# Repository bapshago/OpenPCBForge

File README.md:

# pcbforge

A code-first PCB pipeline with Claude on top. You describe a circuit in
Python (or in plain English, and Claude writes the Python), and pcbforge turns
it into a routed, DRC-checked board plus fab-ready Gerbers.

```
design.py (SKiDL)  ──▶ netlist ──▶ .kicad_pcb (pcbnew API: footprints, outline, placement)
                   ──▶ Freerouting (autoroute via Specctra DSN/SES)
                   ──▶ kicad-cli DRC (JSON) ──▶ Claude reads it and fixes the design
                   ──▶ kicad-cli Gerbers + drill + pick-and-place ──▶ zip
                   ──▶ gerbonara SVG preview of the Gerbers
```

KiCad does the hard geometry: footprints, routing and rule checks. Claude does
what it's good at: turning a spec into a correct circuit, choosing parts,
reading DRC reports and iterating.

**New here?** [`docs/user_guide.md`](docs/user_guide.md) explains, step by step, how to get a
board designed, ordered, built and tested by working with Claude. No setup needed for that.

## Setup

**Ubuntu 24.04:** `./scripts/setup_ubuntu.sh` installs KiCad 9, its libraries,
Java 25 and Freerouting, and creates `.venv`.

**macOS / Windows:** install KiCad 9 from kicad.org and Java 25+ (for
example Temurin), then:

```bash
./scripts/get_freerouting.sh
# Use KiCad's bundled Python so `import pcbnew` works:
#   macOS:   /Applications/KiCad/KiCad.app/Contents/Frameworks/Python.framework/Versions/Current/bin/python3
#   Windows: "C:\Program Files\KiCad\9.0\bin\python.exe"
<kicad-python> -m venv --system-site-packages .venv
.venv/bin/pip install -e '.[dev]'
```

Check that it works: `pytest` runs the blinky board through the full pipeline.

## Usage

```bash
# Build a design file by hand
pcbforge build designs/blinky.py
#   blinky: 3 parts, 3 nets, routed=True
#   DRC: 0 errors, 0 warnings, 0 unconnected
#   Gerbers: build/blinky/blinky-gerbers.zip

# Let Claude design one (needs ANTHROPIC_API_KEY or `ant auth login`)
pcbforge agent "A 30x20mm board: 2-pin header for 5V in, a power LED with a resistor, \
and a tactile button that pulls a 3-pin header's signal pin to ground"
```

Open `build/<name>/<name>.kicad_pcb` in KiCad to inspect or hand-tune the
board. Upload `build/<name>/<name>-gerbers.zip` to your fab (JLCPCB, PCBWay,
OSH Park, and so on). For JLCPCB assembly, also upload `<name>-bom-jlc.csv`
and `<name>-cpl-jlc.csv`.

The agent shows each generated design file and asks before running it,
because a design file is Python that gets executed. `--auto-approve` skips
the prompt.

## JLCPCB files for an existing board

`pcbforge jlc` makes a JLCPCB BOM and CPL (and fresh Gerbers) straight from any
`.kicad_pcb`, including boards drawn by hand or imported from Altium, PADS or Eagle:

```bash
pcbforge jlc path/to/board.kicad_pcb --out build \
    --value-field ALTIUM_VALUE   # field holding the real value, if Value is a placeholder
    --include Q4                 # place a part that also has through-hole pads (e.g. TO-220/DPAK)
    --exclude R99                # leave a part out
    --rotate U7=270              # per-part JLCPCB rotation fix (repeatable)
    --rotate-fp 0805=270         # rotation fix for every part with that footprint name (repeatable)
    --offset=-48.5,200.0         # shift the CPL to match Gerbers made in another tool
    --lcsc L1=C130293            # LCSC number for parts matched by hand (repeatable; R1,R2=C17414 works)
    --move Q4=0,-4.4             # shift one part in the CPL (mm, +y up), e.g. a TO-220/DPAK combo footprint
    --set-value Q2,Q3=IRL540NS   # replace a value (a substitute part, or one the board leaves blank)
    --no-gerbers
```

Resistor and capacitor values are written the way JLCPCB's BOM check reads them
(`4k7` -> `4.7kΩ`, `240R` -> `240Ω`, `100n` -> `100nF`, `2u2` -> `2.2uF`); `--raw-values`
keeps them as drawn. Design-file BOMs from `pcbforge build` get the same treatment.

It places every part whose pads are all SMD, at the centre of its SMD pads (imported
footprints don't always put the origin there), skips values that mean "not fitted"
(na, DNP, ...), and prints what it left out and why: through-hole parts, mixed
SMD/through-hole footprints, and parts with a missing or unknown value.

## JLCPCB parts check

With your own **JLCPCB API key for the parts endpoints** (created at api.jlcpcb.com:
Console → Manage Apps → an app with the Parts APIs approved → Access Key → Create), pcbforge
checks every LCSC number against JLCPCB's records: package against footprint, value, stock
and basic/extended type. Put `JLC_APP_ID`, `JLC_ACCESS_KEY` and `JLC_SECRET_KEY` in `.env`, then:

```bash
pcbforge jlc-auth                                   # check the keys (never prints them)
pcbforge parts-check fab/<board>_rev_a/<board>-bom-jlc.csv [--boards N]
pcbforge jlc-part C25741                            # JLCPCB's full record for a part
```

`pcbforge build` runs the same check when the keys are set. Details and troubleshooting:
`docs/jlcpcb_api.md`.

## Writing a design file

See `designs/blinky.py` for the minimum and `designs/signal_module_928.py`
for a full board. A design file defines:

| Name | Required | Meaning |
|---|---|---|
| `build()` | yes | Creates SKiDL `Part`s (each with `ref=` and `footprint="Lib:Name"`) and connects `Net`s |
| `BOARD` | no | Board settings, below; the origin is top-left with y pointing down |
| `PLACEMENT` | no | `{ref: (x_mm, y_mm, rotation_deg)}`; parts without an entry go on a grid |

`BOARD` keys:

| Key | Meaning |
|---|---|
| `width_mm`, `height_mm` | Board size (a rectangle unless `outline` is given) |
| `outline` | `[(x, y), ...]` closed polygon for a custom shape |
| `holes` | `[(x, y), ...]` M3 mounting holes (`hole_footprint` to change) |
| `silk` | `[(x, y, text, size_mm, rotation), ...]` silkscreen labels |
| `hide_silk_refs` | `True` hides reference designators on the silkscreen (dense boards) |
| `route_passes` | Freerouting passes (default 20; busy boards need more) |
| `clearance_mm` | Copper clearance for every net, default 0.2 mm. 0.15 suits 0.5 mm-pitch ICs (JLCPCB's 2-layer minimum is about 0.127 mm) |
| `route_attempts` | Fresh routing tries, keeping the most complete (default 1) |
| `ground_pour` | Net name, e.g. `"GND"`, to pour on both layers after routing |
| `pour_keepouts` | `[(x1, y1, x2, y2), ...]` areas kept free of poured copper (antennas) |
| `jlc_rotations` | `[(footprint_regex, degrees), ...]` extra JLCPCB placement-rotation fixes, checked before the built-in table in `pcbforge/jlc.py` |
| `jlc_ref_rotations` | `{ref: degrees}` per-part JLCPCB rotation fixes, for parts whose model differs from others in the same package |

Footprints are KiCad 9 library names (`Lib:Name`). `footprints/pcbforge.pretty` holds KiCad
footprints adapted for JLCPCB (for example thermal vias opened to 0.3 mm); use them as
`pcbforge:Name`. See `footprints/README.md`.

Put `part.fields["LCSC"] = "C12084"` (and optionally `"MPN"`) on a part to
carry its LCSC number into the JLCPCB BOM.

**Parts catalogue** (`pcbforge/parts.py`): every part already ordered or checked at JLCPCB,
with its LCSC number. A design can pick one by name (`part(..., **parts.pick("res_0603_10k"))`),
and any part without an LCSC number of its own gets the catalogue's part for its footprint and
value automatically. Each build also writes `<name>-jlc-parts.md`: every BOM line with its LCSC
link, and for parts still to choose, search terms plus JLCPCB and LCSC search links. The BOM's
Footprint column uses JLCPCB's package names (`0603`, `SOIC-8`, `XH-3A 2.5mm`), not KiCad's.

Working on this repo as Claude? Read `docs/claude_playbook.md` first: how boards get
designed, ordered, brought up and documented here, with lessons from the first boards.

## Boards in this repo

| Board | Design | Fab snapshot | Notes |
|---|---|---|---|
| 928 Signal Module rev A (**installed in the '81**, Nov 1 2026) | `designs/signal_module_928.py` | `fab/signal_module_928_rev_a/` | `docs/signal_module_928_handoff.md`, firmware in `firmware/signal_module_928/` |
| 928 Heater Controller rev A (in production) | `designs/heater_controller_928.py` | `fab/heater_controller_928_rev_a/` | `docs/heater_controller_928.md` |
| `designs/blinky.py` | the smallest example: 3 parts | built by `pytest` | |

The two 928 boards were made for a 1981 Porsche 928 converted to a Nissan Leaf drivetrain, and
share a 60 x 90 mm outline and mounting holes. They're real, ordered boards, included as
worked examples: a design file, the exact files sent to JLCPCB, and a connection test
(`tests/test_<board>.py`) that checks every pin against the datasheets. The signal module's
hardware and firmware are also published on their own at
[bapshago/928-Signal-Board](https://github.com/bapshago/928-Signal-Board).

## Layout

| Path | Role |
|---|---|
| `pcbforge/netlist.py` | Runs the design file with SKiDL, then ERC and netlist |
| `pcbforge/board.py` | Builds the `.kicad_pcb` with pcbnew: outline, nets, footprints, placement |
| `pcbforge/route.py` | Freerouting round-trip |
| `pcbforge/pour.py` | Optional ground pour with keepouts |
| `pcbforge/drc.py` | `kicad-cli pcb drc`, summarized |
| `pcbforge/export.py` | Gerbers, drill file, pick-and-place, zip |
| `pcbforge/jlc.py` | JLCPCB BOM, CPL and parts list |
| `pcbforge/parts.py` | Parts catalogue: parts already ordered at JLCPCB, used by default |
| `pcbforge/jlcapi.py`, `pcbforge/partcheck.py` | JLCPCB Open API client and part check: package, value and stock of every LCSC number (`pcbforge parts-check`; see `docs/jlcpcb_api.md`) |
| `pcbforge/preview.py` | Renders the Gerbers to SVG with gerbonara |
| `pcbforge/pipeline.py` | Runs all of the above in order |
| `pcbforge/agent.py` | Claude tool-use agent (symbol/footprint lookup, write design, build) |
| `pcbforge/env.py` | KiCad paths and tool locations, each overridable by env var |

## Good next steps

1. **Smarter placement.** Group parts by net connectivity (force-directed
   placement or simulated annealing) so routes are short. Have Claude supply
   the constraints ("decoupling caps next to U1's VDD pins", "connectors on
   the edge") rather than coordinates.
2. **Schematic output.** SKiDL can generate KiCad schematics, which makes
   human review much easier.
3. **Net classes.** Wider traces for power nets (design settings) before routing.
4. **Part search for the agent.** The JLCPCB parts check is done (`docs/jlcpcb_api.md`);
   next, a local copy of JLCPCB's catalogue so the agent can search it for parts.
5. **Fab-specific DRC.** Load your fab's design rules (`.kicad_dru`) so DRC
   matches what they can manufacture.

## Gotchas

- **Java version:** Freerouting 2.4 needs Java 25+. Set `JAVA=/path/to/java25`
  if the default `java` is older.
- **SKiDL tool version:** SKiDL defaults to KiCad 10 libraries. pcbforge pins
  KiCad 9; change `SKIDL_TOOL` when you upgrade.
- **`pcbnew` import errors:** the venv must use the same Python that KiCad was
  built against, with `--system-site-packages`.

## Built on

pcbforge is mostly glue between these projects, and wouldn't exist without them. Thank you
to their authors and maintainers.

| Project | What it does in pcbforge | License |
|---|---|---|
| [SKiDL](https://github.com/devbisme/skidl) by Dave Vandenbout | Runs the Python design file: parts, nets, the electrical rules check (ERC) and the netlist | MIT |
| [KiCad](https://www.kicad.org) | The `pcbnew` Python API builds the board; `kicad-cli` runs DRC and writes Gerbers, drill and placement files; its symbol and footprint libraries supply every part | GPL-3.0-or-later; libraries CC-BY-SA 4.0 with an exception for designs that use them |
| [Freerouting](https://github.com/freerouting/freerouting) | Autoroutes the board | GPL-3.0 |
| [gerbonara](https://gitlab.com/gerbolyze/gerbonara) by jaseg and XenGi | Renders the Gerbers to an SVG preview | Apache-2.0 |
| [Anthropic Python SDK](https://github.com/anthropics/anthropic-sdk-python) | The design agent's calls to Claude | MIT |

They're installed separately (see Setup) and keep their own licenses. The footprint in
`footprints/pcbforge.pretty` is a modified KiCad library footprint and stays under the KiCad
libraries' license.

## Contributing

pcbforge was written for one person's projects and shared in case it's useful to others.
Issues and pull requests are welcome: bug reports with the design file and the build output,
new parts for the catalogue (with their LCSC numbers and where they were checked), JLCPCB
rotation fixes confirmed in their placement preview, and the "Good next steps" above.
Run `pytest` before sending a change; it needs KiCad 9 for the board tests (they skip
without it).

## License

MIT, see [LICENSE](LICENSE). The example board designs and fab files are covered too.
The tools it builds on keep their own licenses: see Built on.

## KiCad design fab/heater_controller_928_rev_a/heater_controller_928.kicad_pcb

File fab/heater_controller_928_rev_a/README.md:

# 928 Heater Controller: board rev A fabrication snapshot

Generated by `pcbforge build designs/heater_controller_928.py`. KiCad DRC: **0 errors, 0 warnings, 0 unconnected**.

Same 60 x 90 mm outline, corner notches and M3 holes as the signal module. Built for the
ESP32-S3-DevKitC-1 (header rows 22.86 mm apart). Board notes, connector pinouts and GPIO map:
`docs/heater_controller_928.md`.

Ordered Oct 23, 2026: 5 boards (green, 1.6 mm, ENIG), all 5 assembled by JLCPCB (top side), about $127 before shipping.
The pulled files went through with no manual fixes. Every assembled part carries the LCSC number it
was ordered with. Y1 (8 MHz crystal for the MCP2515 / CAN B) was added by hand in JLCPCB's BOM tool as C57131. U7's rotation fix from JLCPCB's preview (90° clockwise) is now built into the
CPL file, so a re-order should need no manual fixes.

Nov 5, 2026: in production, after JLCPCB's hold on R21-R32 (C723496 is 01005) was fixed with C25741.
`pcbforge parts-check` on `heater_controller_928-bom-jlc.csv` passes with 0 errors.

| File | Use |
|---|---|
| `heater_controller_928.kicad_pcb` (+ `.kicad_pro`, `fp-lib-table`) | Open in KiCad 9 to inspect or hand-tune |
| `heater_controller_928-gerbers.zip` | Upload to JLCPCB as the PCB (2 layers, 1.6 mm) |
| `heater_controller_928-bom-jlc.csv` | JLCPCB assembly: BOM |
| `heater_controller_928-cpl-jlc.csv` | JLCPCB assembly: placement (CPL) |
| `heater_controller_928-bom-as-ordered.csv` | The BOM JLCPCB confirmed for the first order, for reference |
| `heater_controller_928-not-placed-by-jlc.csv` | Parts JLCPCB did not place (connectors, sockets, headers) |
| `heater_controller_928-drc.json` | KiCad rule-check report |

If you change the design file, rebuild and copy the new outputs here; this folder is a
snapshot, not regenerated automatically.

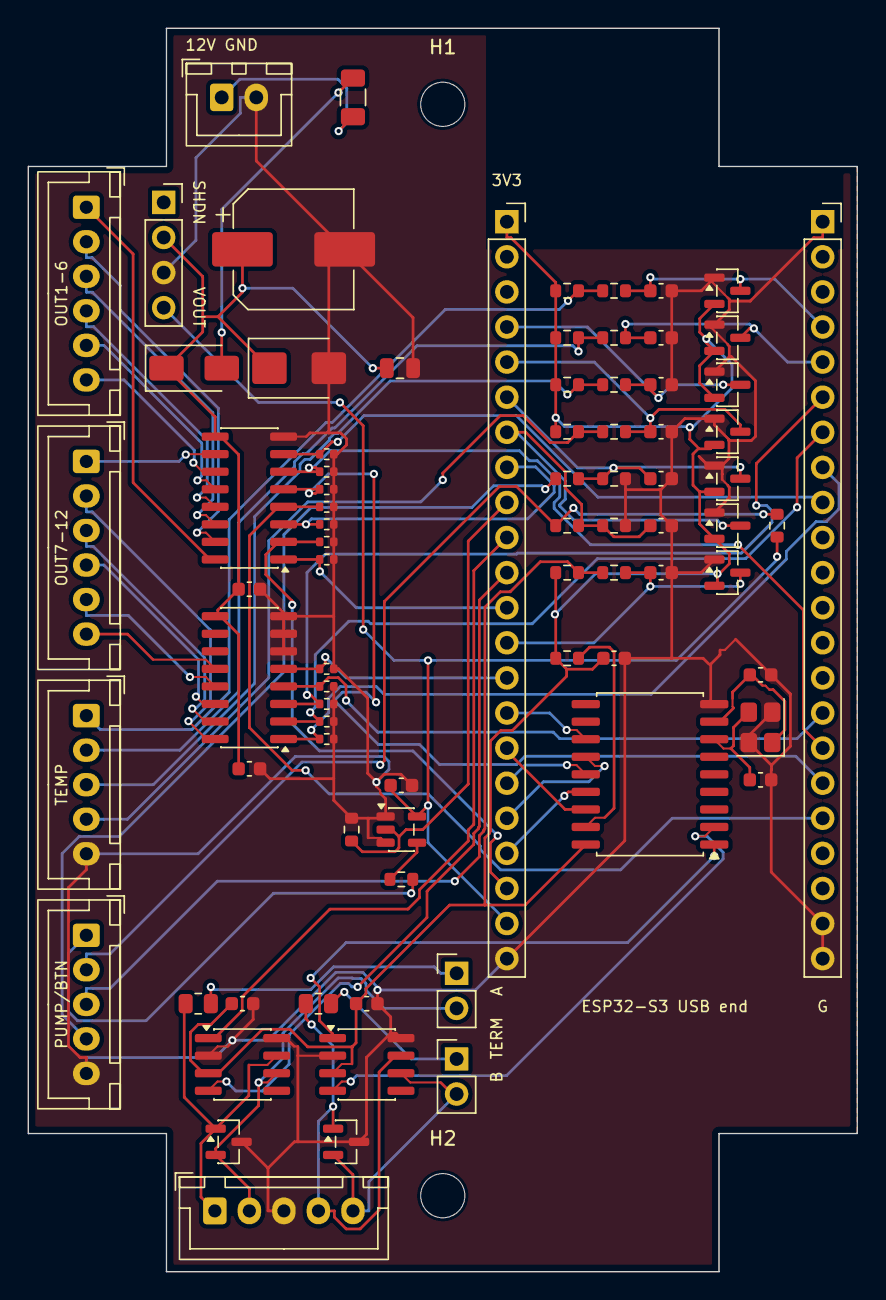
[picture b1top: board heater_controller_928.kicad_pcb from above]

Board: 2 copper layers, 60.0 x 90.0 mm, 81 parts (0 on the bottom side), 65 nets.

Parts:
C10: 47u 63V; CP_Elec_8x10.5
C11: 100n 100V; C_0805_2012Metric
C12, C13, C14, C20, C21, C41, C42, C43, C44, C51, C54: 100n; C_0603_1608Metric
C15, C16: 22p; C_0603_1608Metric
C52: 1n; C_0603_1608Metric
C53: 10n; C_0603_1608Metric
D10: SS34; D_SMA
D11: SMBJ24A; D_SMB
D20, D21: NUP2105L; SOT-23
D41, D42, D43, D44, D51, D52, D53: BAT54S; SOT-23
F1: 1A; Fuse_1206_3216Metric
H1, H2: MountingHole_3.2mm_M3
J1: PWR; JST_XH_B2B-XH-A_1x02_P2.50mm_Vertical
J2: CAN A/B; JST_XH_B5B-XH-A_1x05_P2.50mm_Vertical
J4: OUT1-6; JST_XH_B6B-XH-A_1x06_P2.50mm_Vertical
J5: OUT7-12; JST_XH_B6B-XH-A_1x06_P2.50mm_Vertical
J6: TEMP; JST_XH_B5B-XH-A_1x05_P2.50mm_Vertical
J7: PUMP/BTN; JST_XH_B5B-XH-A_1x05_P2.50mm_Vertical
J9: Pololu D36V6F5; PinSocket_1x04_P2.54mm_Vertical
J10: DevKit J1; PinSocket_1x22_P2.54mm_Vertical
J11: DevKit J3; PinSocket_1x22_P2.54mm_Vertical
JP1, JP2: TERM; PinHeader_1x02_P2.54mm_Vertical
R10, R11: 120; R_0805_2012Metric
R12, R52, R54, R56: 10k; R_0603_1608Metric
R21, R22, R23, R24, R25, R26, R27, R28, R29, R30, R31, R32: 100k; R_0402_1005Metric
R41, R43, R45, R47: 2.2k 1%; R_0603_1608Metric
R42, R44, R46, R48, R57: 1k; R_0603_1608Metric
R51: 47k; R_0603_1608Metric
R53: 4.7k; R_0603_1608Metric
R55: 22k; R_0603_1608Metric
R58: 100k; R_0603_1608Metric
R59: 100; R_0603_1608Metric
U2, U4: SN65HVD230DR; SOIC-8_3.9x4.9mm_P1.27mm
U3: MCP2515; SOIC-18W_7.5x11.6mm_P1.27mm
U5, U6: TPL7407L; SOIC-16_3.9x9.9mm_P1.27mm
U7: 74AHCT1G125; SOT-23-5
Y1: 8MHz; Crystal_SMD_3225-4Pin_3.2x2.5mm

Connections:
+3V3: C12.1, C13.1, C14.1, D41.2, D42.2, D43.2, D44.2, D51.2, D52.2, D53.2, J10.1, R12.1, R41.1, R43.1, R45.1, R47.1, R56.1, U2.3, U3.18, U4.3
+5V: C54.1, J9.4, J10.21, R53.1, U7.5
+12V_FUSED: D10.2, F1.2
+12V_IN: F1.1, J1.1
+12V_SW: C10.1, C11.1, C20.1, C21.1, D10.1, D11.1, J9.2, U5.9, U6.9
BLW_I: J4.2, U5.15
BLW_II: J4.3, U5.14
BLW_III: J4.4, U5.13
BLW_III_GPIO21: J11.18, R24.1, U5.4
BLW_II_GPIO15: J10.8, R23.1, U5.3
BLW_IV: J4.5, U5.12
BLW_IV_GPIO47: J11.17, R25.1, U5.5
BLW_I_GPIO14: J10.20, R22.1, U5.2
BLW_MASTER: J4.1, U5.16
BLW_MASTER_GPIO8: J10.12, R21.1, U5.1
BTN_GPIO3: C53.1, D53.3, J10.13, R57.2
BTN_IN: J7.3, R56.2, R57.1
CANA_H: D20.1, J2.1, R10.1, U2.7
CANA_H_TERM: JP1.1, R10.2
CANA_L: D20.2, J2.2, JP1.2, U2.6
CANA_RX_GPIO18: J10.11, U2.4
CANA_TX_GPIO17: J10.10, U2.1
CANB_H: D21.1, J2.4, R11.1, U4.7
CANB_H_TERM: JP2.1, R11.2
CANB_INT_GPIO9: J10.15, U3.12
CANB_L: D21.2, J2.5, JP2.2, U4.6
CANB_OSC1: C15.1, U3.8, Y1.1
CANB_OSC2: C16.1, U3.7, Y1.3
CANB_RESET: R12.2, U3.17
CANB_RX: U3.2, U4.4
CANB_TX: U3.1, U4.1
GND: C10.2, C11.2, C12.2, C13.2, C14.2, C15.2, C16.2, C20.2, C21.2, C41.2, C42.2, C43.2, C44.2, C51.2, C52.2, C53.2, C54.2, D11.2, D20.3, D21.3, D41.1, D42.1, D43.1, D44.1, D51.1, D52.1, D53.1, J1.2, J2.3, J6.5, J7.5, J9.3, J10.22, J11.1, J11.21, J11.22, R21.2, R22.2, R23.2, R24.2, R25.2, R26.2, R27.2, R28.2, R29.2, R30.2, R31.2, R32.2, R52.2, R55.2, R58.2, U2.2, U2.8, U3.9, U4.2, U4.8, U5.8, U6.6, U6.7, U6.8, U7.1, U7.3, Y1.2, Y1.4
HTR_RLY: J5.1, U5.10
HTR_RLY_GPIO39: J11.9, R27.1, U5.7
HTR_SENSE_GPIO6: C51.1, D51.3, J10.6, R51.2, R52.1
HTR_SENSE_IN: J7.4, R51.1
PUMP_FB_GPIO7: C52.1, D52.3, J10.7, R54.2, R55.1
PUMP_FB_IN: J7.2, R53.2, R54.1
PUMP_PWM_5V: R59.1, U7.4
PUMP_PWM_GPIO16: J10.9, R58.1, U7.2
PUMP_PWM_OUT: J7.1, R59.2
PUMP_RLY: J4.6, U5.11
PUMP_RLY_GPIO48: J11.16, R26.1, U5.6
SOL_COOLANT: J5.2, U6.16
SOL_COOLANT_GPIO40: J11.8, R28.1, U6.1
SOL_DEFROST: J5.5, U6.13
SOL_DEFROST_GPIO45: J11.15, R31.1, U6.4
SOL_FOOT: J5.6, U6.12
SOL_FOOT_GPIO46: J10.14, R32.1, U6.5
SOL_IMPACT: J5.3, U6.15
SOL_IMPACT_GPIO41: J11.7, R29.1, U6.2
SOL_RECIRC: J5.4, U6.14
SOL_RECIRC_GPIO42: J11.6, R30.1, U6.3
SPI_CS_GPIO10: J10.16, U3.16
SPI_MISO_GPIO13: J10.19, U3.15
SPI_MOSI_GPIO11: J10.17, U3.14
SPI_SCK_GPIO12: J10.18, U3.13
T_CABIN_GPIO4: C43.1, D43.3, J10.4, R46.2
T_CABIN_IN: J6.3, R45.2, R46.1
T_OUTLET_GPIO1: C41.1, D41.3, J11.4, R42.2
T_OUTLET_IN: J6.1, R41.2, R42.1
T_RETURN_GPIO2: C42.1, D42.3, J11.5, R44.2
T_RETURN_IN: J6.2, R43.2, R44.1
T_SPARE_GPIO5: C44.1, D44.3, J10.5, R48.2
T_SPARE_IN: J6.4, R47.2, R48.1

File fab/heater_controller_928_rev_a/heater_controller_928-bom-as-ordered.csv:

Comment,Designator,Footprint,JLCPCB Part #
10n,C53,C_0603_1608Metric,C57112
1A,F1,Fuse_1206_3216Metric,C151135
47k,R51,R_0603_1608Metric,C25819
1n,C52,C_0603_1608Metric,C1588
BAT54S,"D41,D42,D43,D44,D51,D52,D53",SOT-23,C7420333
100n,"C12,C13,C14,C20,C21,C41,C42,C43,C44,C51,C54",C_0603_1608Metric,C14663
TPL7407L,"U5,U6",SOIC-16_3.9x9.9mm_P1.27mm,C139663
SN65HVD230DR,"U2,U4",SOIC-8_3.9x4.9mm_P1.27mm,C12084
22k,R55,R_0603_1608Metric,C31850
SS34,D10,D_SMA,C8678
120,"R10,R11",R_0805_2012Metric,C54921099
NUP2105L,"D20,D21",SOT-23,C284104
100n100V,C11,C_0805_2012Metric,C28233
2.2k1%,"R41,R43,R45,R47",R_0603_1608Metric,C2907005
74AHCT1G125,U7,SOT-23-5,C52140417
100,R59,R_0603_1608Metric,C22775
MCP2515,U3,SOIC-18W_7.5x11.6mm_P1.27mm,C153782
SMBJ24A,D11,D_SMB,C5178956
47u63V,C10,CP_Elec_8x10.5,C82011
4.7k,R53,R_0603_1608Metric,C23162
10k,"R12,R52,R54,R56",R_0603_1608Metric,C25804
1k,"R42,R44,R46,R48,R57",R_0603_1608Metric,C21190
100k,R58,R_0603_1608Metric,C25803
22p,"C15,C16",C_0603_1608Metric,C1653
100k,"R21,R22,R23,R24,R25,R26,R27,R28,R29,R30,R31,R32",R_0402_1005Metric,C723496
8MHz 12pF,Y1,Crystal_SMD_3225-4Pin_3.2x2.5mm,C57131

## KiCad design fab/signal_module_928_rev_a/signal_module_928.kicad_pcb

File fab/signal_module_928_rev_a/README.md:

# 928 Signal Module: board rev A fabrication snapshot

Generated by `pcbforge build designs/signal_module_928.py`. KiCad DRC: **0 errors, 0 warnings, 0 unconnected**.

Built for the AITRIP 38-pin ESP32 board (header rows 22.86 mm apart).

Ordered: 5 boards with JLCPCB SMT assembly (Oct 2026). Every assembled part now
carries the LCSC number it was ordered with, and the CPL rotations match what
was confirmed in JLCPCB's preview, so a re-order should need no manual fixes.
Still glance at the preview: JLCPCB changes part models occasionally.

| File | Use |
|---|---|
| `signal_module_928.kicad_pcb` (+ `.kicad_pro`, `fp-lib-table`) | Open in KiCad 9 to inspect or hand-tune |
| `signal_module_928-gerbers.zip` | Upload to JLCPCB as the PCB (2 layers, 1.6 mm) |
| `signal_module_928-bom-jlc.csv` | JLCPCB assembly: BOM |
| `signal_module_928-cpl-jlc.csv` | JLCPCB assembly: placement (CPL), rotations already corrected for JLCPCB's part models |
| `signal_module_928-bom-as-ordered.csv` | The BOM JLCPCB confirmed for the first order (5 boards, Oct 2026), for reference |
| `signal_module_928-drc.json` | KiCad rule-check report |

If you change the design file, rebuild and copy the new outputs here; this
folder is a snapshot, not regenerated automatically.

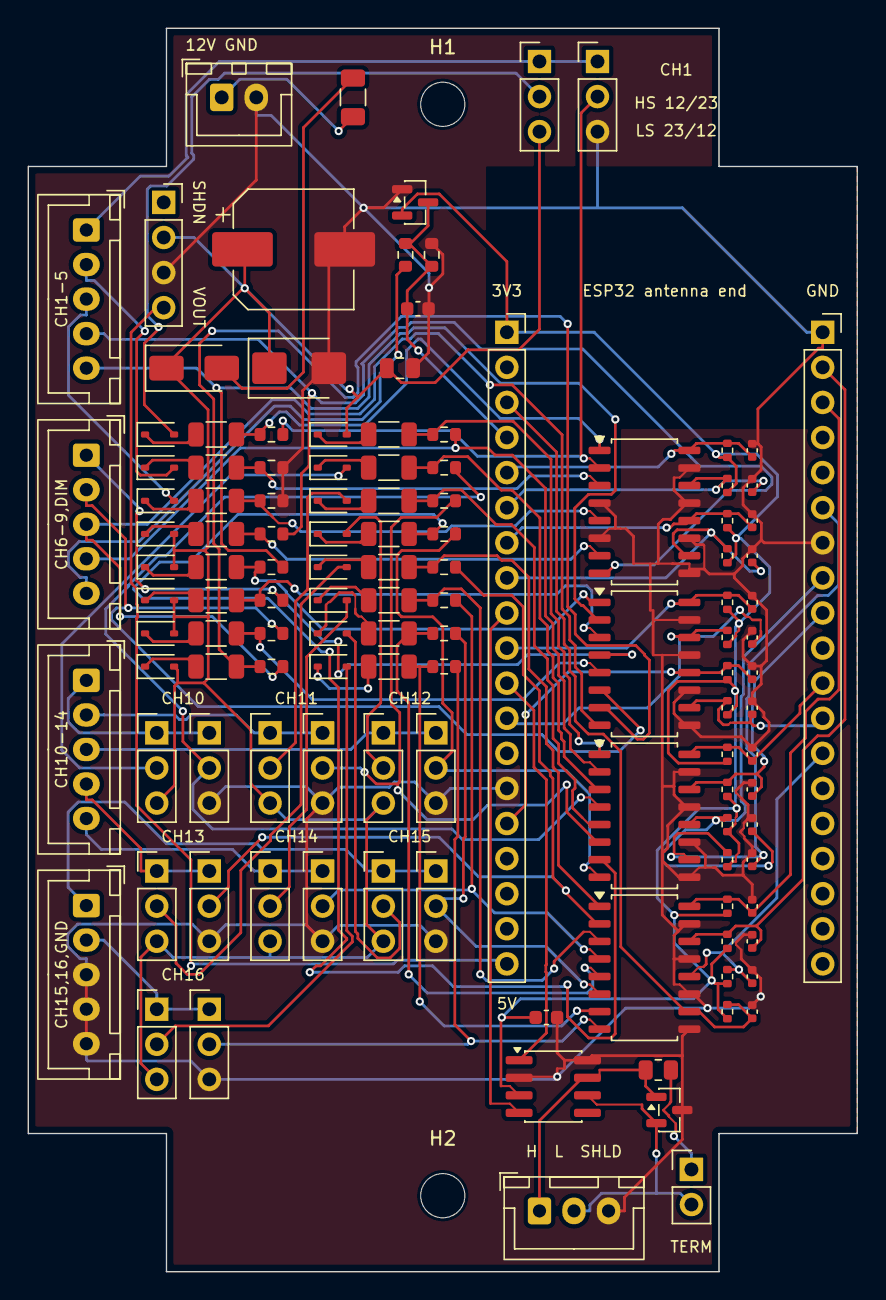
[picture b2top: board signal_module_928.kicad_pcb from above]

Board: 2 copper layers, 60.0 x 90.0 mm, 125 parts (0 on the bottom side), 93 nets.

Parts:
C2, C12: 100n; C_0603_1608Metric
C10: 47u 63V; CP_Elec_8x10.5
C11: 100n 100V; C_0805_2012Metric
C101, C102, C103, C104, C105, C106, C107, C108, C109, C110, C111, C112, C113, C114, C115, C116: 10n; C_0402_1005Metric
D3: BAT54S; SOT-23
D10: SS34; D_SMA
D11: SMBJ24A; D_SMB
D12: NUP2105L; SOT-23
D101, D102, D103, D104, D105, D106, D107, D108, D109, D110, D111, D112, D113, D114, D115, D116: 1N4148WS; D_SOD-323
F1: 1A; Fuse_1206_3216Metric
H1, H2: MountingHole_3.2mm_M3
J1: PWR 3R/9R; JST_XH_B2B-XH-A_1x02_P2.50mm_Vertical
J2: CAN; JST_XH_B3B-XH-A_1x03_P2.50mm_Vertical
J3: Inputs CH1-5; JST_XH_B5B-XH-A_1x05_P2.50mm_Vertical
J4: Inputs CH6-9,DIM; JST_XH_B5B-XH-A_1x05_P2.50mm_Vertical
J5: Inputs CH10-14; JST_XH_B5B-XH-A_1x05_P2.50mm_Vertical
J6: Inputs CH15,16,GND; JST_XH_B5B-XH-A_1x05_P2.50mm_Vertical
J7: DevKitC J2; PinSocket_1x19_P2.54mm_Vertical
J8: DevKitC J3; PinSocket_1x19_P2.54mm_Vertical
J9: Pololu D36V6F5; PinSocket_1x04_P2.54mm_Vertical
JP10: TERM; PinHeader_1x02_P2.54mm_Vertical
JP101: CH1 JP1; PinHeader_1x03_P2.54mm_Vertical
JP110: CH10 JP1; PinHeader_1x03_P2.54mm_Vertical
JP111: CH11 JP1; PinHeader_1x03_P2.54mm_Vertical
JP112: CH12 JP1; PinHeader_1x03_P2.54mm_Vertical
JP113: CH13 JP1; PinHeader_1x03_P2.54mm_Vertical
JP114: CH14 JP1; PinHeader_1x03_P2.54mm_Vertical
JP115: CH15 JP1; PinHeader_1x03_P2.54mm_Vertical
JP116: CH16 JP1; PinHeader_1x03_P2.54mm_Vertical
JP201: CH1 JP2; PinHeader_1x03_P2.54mm_Vertical
JP210: CH10 JP2; PinHeader_1x03_P2.54mm_Vertical
JP211: CH11 JP2; PinHeader_1x03_P2.54mm_Vertical
JP212: CH12 JP2; PinHeader_1x03_P2.54mm_Vertical
JP213: CH13 JP2; PinHeader_1x03_P2.54mm_Vertical
JP214: CH14 JP2; PinHeader_1x03_P2.54mm_Vertical
JP215: CH15 JP2; PinHeader_1x03_P2.54mm_Vertical
JP216: CH16 JP2; PinHeader_1x03_P2.54mm_Vertical
R4: 47k; R_0603_1608Metric
R5, R201, R202, R203, R204, R205, R206, R207, R208, R209, R210, R211, R212, R213, R214, R215, R216: 10k; R_0603_1608Metric
R10: 120; R_0805_2012Metric
R101, R102, R103, R104, R105, R106, R107, R108, R109, R110, R111, R112, R113, R114, R115, R116: 2.2k; R_1206_3216Metric
R301, R302, R303, R304, R305, R306, R307, R308, R309, R310, R311, R312, R313, R314, R315, R316: 10k; R_0402_1005Metric
U2: SN65HVD230DR; SOIC-8_3.9x4.9mm_P1.27mm
U3, U4, U5, U6: TLP291-4; SOIC-16_4.55x10.3mm_P1.27mm

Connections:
+3V3: C12.1, D3.2, J7.1, R301.1, R302.1, R303.1, R304.1, R305.1, R306.1, R307.1, R308.1, R309.1, R310.1, R311.1, R312.1, R313.1, R314.1, R315.1, R316.1, U2.3
+5V: J7.19, J9.4
+12V_FUSED: D10.2, F1.2
+12V_IN: F1.1, J1.1
+12V_SW: C10.1, C11.1, D10.1, D11.1, D104.2, D105.2, D106.2, D107.2, D108.2, D109.2, J9.2, JP101.3, JP110.3, JP111.3, JP112.3, JP113.3, JP114.3, JP115.3, JP116.3
CANH: D12.1, J2.1, R10.1, U2.7
CANL: D12.2, J2.2, JP10.2, U2.6
CAN_RX: J7.9, U2.4
CAN_TERM: JP10.1, R10.2
CAN_TX: J7.11, U2.1
CH1_D1_A: D101.2, JP101.2
CH1_GPIO34: C101.1, J7.5, R301.2, U3.16
CH1_IN: J3.1, JP101.1, JP201.1
CH1_LED_A: R101.2, R201.1, U3.1
CH1_LED_K: JP201.2, R201.2, U3.2
CH2_GPIO35: C102.1, J7.6, R302.2, U3.14
CH2_IN: D102.2, J3.2
CH2_LED_A: R102.2, R202.1, U3.3
CH3_GPIO32: C103.1, J7.7, R303.2, U3.12
CH3_IN: D103.2, J3.3
CH3_LED_A: R103.2, R203.1, U3.5
CH4_GPIO33: C104.1, J7.8, R304.2, U3.10
CH4_IN: J3.4, R204.2, U3.8
CH4_LED_A: R104.2, R204.1, U3.7
CH5_GPIO26: C105.1, J7.10, R305.2, U4.16
CH5_IN: J3.5, R205.2, U4.2
CH5_LED_A: R105.2, R205.1, U4.1
CH6_GPIO14: C106.1, J7.12, R306.2, U4.14
CH6_IN: J4.1, R206.2, U4.4
CH6_LED_A: R106.2, R206.1, U4.3
CH7_GPIO13: C107.1, J7.15, R307.2, U4.12
CH7_IN: J4.2, R207.2, U4.6
CH7_LED_A: R107.2, R207.1, U4.5
CH8_GPIO16: C108.1, J8.12, R308.2, U4.10
CH8_IN: J4.3, R208.2, U4.8
CH8_LED_A: R108.2, R208.1, U4.7
CH9_GPIO17: C109.1, J8.11, R309.2, U5.16
CH9_IN: J4.4, R209.2, U5.2
CH9_LED_A: R109.2, R209.1, U5.1
CH10_D1_A: D110.2, JP110.2
CH10_GPIO18: C110.1, J8.9, R310.2, U5.14
CH10_IN: J5.1, JP110.1, JP210.1
CH10_LED_A: R110.2, R210.1, U5.3
CH10_LED_K: JP210.2, R210.2, U5.4
CH11_D1_A: D111.2, JP111.2
CH11_GPIO19: C111.1, J8.8, R311.2, U5.12
CH11_IN: J5.2, JP111.1, JP211.1
CH11_LED_A: R111.2, R211.1, U5.5
CH11_LED_K: JP211.2, R211.2, U5.6
CH12_D1_A: D112.2, JP112.2
CH12_GPIO21: C112.1, J8.6, R312.2, U5.10
CH12_IN: J5.3, JP112.1, JP212.1
CH12_LED_A: R112.2, R212.1, U5.7
CH12_LED_K: JP212.2, R212.2, U5.8
CH13_D1_A: D113.2, JP113.2
CH13_GPIO22: C113.1, J8.3, R313.2, U6.16
CH13_IN: J5.4, JP113.1, JP213.1
CH13_LED_A: R113.2, R213.1, U6.1
CH13_LED_K: JP213.2, R213.2, U6.2
CH14_D1_A: D114.2, JP114.2
CH14_GPIO23: C114.1, J8.2, R314.2, U6.14
CH14_IN: J5.5, JP114.1, JP214.1
CH14_LED_A: R114.2, R214.1, U6.3
CH14_LED_K: JP214.2, R214.2, U6.4
CH15_D1_A: D115.2, JP115.2
CH15_GPIO4: C115.1, J8.13, R315.2, U6.12
CH15_IN: J6.1, JP115.1, JP215.1
CH15_LED_A: R115.2, R215.1, U6.5
CH15_LED_K: JP215.2, R215.2, U6.6
CH16_D1_A: D116.2, JP116.2
CH16_GPIO36: C116.1, J7.3, R316.2, U6.10
CH16_IN: J6.2, JP116.1, JP216.1
CH16_LED_A: R116.2, R216.1, U6.7
CH16_LED_K: JP216.2, R216.2, U6.8
DIM_ADC: C2.1, D3.3, J7.4, R4.2, R5.1
DIM_IN: J4.5, R4.1
GND: C2.2, C10.2, C11.2, C12.2, C101.2, C102.2, C103.2, C104.2, C105.2, C106.2, C107.2, C108.2, C109.2, C110.2, C111.2, C112.2, C113.2, C114.2, C115.2, C116.2, D3.1, D11.2, D12.3, J1.2, J2.3, J6.3, J6.4, J6.5, J7.14, J8.1, J8.7, J9.3, JP201.3, JP210.3, JP211.3, JP212.3, JP213.3, JP214.3, JP215.3, JP216.3, R5.2, R202.2, R203.2, U2.2, U2.8, U3.4, U3.6, U3.9, U3.11, U3.13, U3.15, U4.9, U4.11, U4.13, U4.15, U5.9, U5.11, U5.13, U5.15, U6.9, U6.11, U6.13, U6.15
unnamed: D101.1, R101.1
unnamed: D102.1, R102.1
unnamed: D103.1, R103.1
unnamed: D104.1, R104.1
unnamed: D105.1, R105.1
unnamed: D106.1, R106.1
unnamed: D107.1, R107.1
unnamed: D108.1, R108.1
unnamed: D109.1, R109.1
unnamed: D110.1, R110.1
unnamed: D111.1, R111.1
unnamed: D112.1, R112.1
unnamed: D113.1, R113.1
unnamed: D114.1, R114.1
unnamed: D115.1, R115.1
unnamed: D116.1, R116.1

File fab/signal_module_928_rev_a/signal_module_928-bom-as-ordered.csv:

Comment,Designator,Footprint,JLCPCB Part #,Qty,Ext.Price($)
10k,"R301,R302,R303,R304,R305,R306,R307,R308,R309,R310,R311,R312,R313,R314,R315,R316",R_0402_1005Metric,C60490,90,0.21
47u63V,C10,CP_Elec_8x10.5,C82011,6,1.09
1A,F1,Fuse_1206_3216Metric,C151135,7,0.67
120,R10,R_0805_2012Metric,C54921099,20,0.04
NUP2105L,D12,SOT-23,C284104,9,0.52
47k,R4,R_0603_1608Metric,C25819,5,0.02
100n100V,C11,C_0805_2012Metric,C28233,5,0.12
TLP291-4,"U3,U4,U5,U6",SOIC-16_4.55x10.3mm_P1.27mm,C60900,20,10.69
1N4148WS,"D101,D102,D103,D104,D105,D106,D107,D108,D109,D110,D111,D112,D113,D114,D115,D116",D_SOD-323,C2128,80,1.12
BAT54S,D3,SOT-23,C7420333,10,0.13
100n,"C2,C12",C_0603_1608Metric,C14663,10,0.08
SN65HVD230DR,U2,SOIC-8_3.9x4.9mm_P1.27mm,C12084,5,2.86
10nF50VX7R0402,"C101,C102,C103,C104,C105,C106,C107,C108,C109,C110,C111,C112,C113,C114,C115,C116",C_0402_1005Metric,C15195,80,0.33
SMBJ24A,D11,D_SMB,C5178956,9,0.42
SS34,D10,D_SMA,C8678,5,0.18
10k,"R5,R201,R202,R203,R204,R205,R206,R207,R208,R209,R210,R211,R212,R213,R214,R215,R216",R_0603_1608Metric,C25804,85,0.15
2.2k,"R101,R102,R103,R104,R105,R106,R107,R108,R109,R110,R111,R112,R113,R114,R115,R116",R_1206_3216Metric,C2930413,90,0.50

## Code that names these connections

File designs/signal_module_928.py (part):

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        sock, pin = gpio_pin[gpio]
        sock[pin] += ch_gpio[n]
    sock, pin = gpio_pin[39]
    sock[pin] += dim_adc
    sock, pin = gpio_pin[25]
    sock[pin] += can_rx
    sock, pin = gpio_pin[27]
    sock[pin] += can_tx
    silk(DEVKIT_X_LEFT, DEVKIT_Y_PIN1 - 3.0, "3V3", 0.8)
    silk(DEVKIT_X_RIGHT, DEVKIT_Y_PIN1 - 3.0, "GND", 0.8)
    silk((DEVKIT_X_LEFT + DEVKIT_X_RIGHT) / 2, DEVKIT_Y_PIN1 - 3.0, "ESP32 antenna end", 0.8)
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    u2["GND"] += gnd
    u2["Rs"] += gnd      # Rs to GND = high-speed mode
    u2["CANH"] += canh
    u2["CANL"] += canl   # Vref (pin 5) left open

    c12 = place(part("Device", "C", "C12", "100n", FP_C0603, lcsc="C14663", mpn="CC0603KRX7R9BB104"), 37.5, 71.6)
    c12[1, 2] += v3, gnd
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    silk(39.5, 81.3, "H  L  SHLD", 0.8)

    # ------------------------------------------------------------ dash dimmer (sheet 2 D)
    j4_dim = dim_in  # lands on J4 pin 5 below
    r4 = place(part("Device", "R", "R4", "47k", FP_R0603, lcsc="C25819", mpn="0603WAF4702T5E"), 27.3, 16.4, 90)
    r4[1, 2] += j4_dim, dim_adc
    r5 = place(part("Device", "R", "R5", "10k", FP_R0603, lcsc="C25804", mpn="0603WAF1002T5E"), 29.2, 16.4, 90)
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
